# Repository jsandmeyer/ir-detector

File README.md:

## IR Reflection Detector

This provides resources to help you build an IR detector for use with O-scale model railroad track in order to detect passing trains for operating block signals.

It is designed to be placed beneath the tracks, to allow for the use of more realistic trackside accessories and buildings.

It emits and detects IR at 38KHz (though the frequency can be changed based on part choice).
This prevents background light from affecting function.

The original analog designs utilized a TLC555 CMOS timer.
The timer was unstable through stray capacitance caused by rail operation, and also likely by temperature fluctuations from the power supply.
Small microcontrollers like the ATTINY family are inexpensive, simple to program, and more stable even without an external clock.

The current versions utilize a switching power supply to avoid heat, so the device can be safely placed under track.
The input voltage is 18V RMS AC, which rectifies to 26V DC.
Since only 3-5 volts are needed for the circuit, power dissipation through a linear supply is excessive.

### Design Requirements

1. Must be able to handle 18V RMS AC (or a little more)
2. Must be able to handle rapid shutoff of power
3. Must avoid producing noticeable heat
4. Must fit hidden under track
   1. Shape limits (avoid track supports, power connectors, etc)
   2. Size limits (must not extend past track base, must have a way to feed wires)
   3. Some components must be aligned under a single oblong hole in track base
5. Emitter LED must be shrouded to avoid directly triggering detector
6. Must handle stray capacitance, excessive heat, and some signal interference
7. Must be small to reduce cost, especially when a 4-layer design is used

### Circuit Parts

1. MCU: Responsible for PWM to control the IR emitter, and controlling the relay when a reflection is detected.
2. Switching Power Supply: reduce up to 35VDC input to 3V output for the MCU, IR LED, and relay.
3. IR LED: an emitter running at ~70mA, and 50% duty cycle at 36-56KHz depending on detector part selection.
4. IR Detector: an IC containing both a detector and frequency detection logic, to ensure only correct-frequency light is detected.  36, 38, 40, or 56 KHz.
5. Relay: Controls AC (or DC) current from inputs to a normally-open and normally-closed output.
6. Trimmer: Controls duration of relay after IR is no longer detected.

### Design Versions

Some versions are skipped.
Those were only built on breadboard, or designed and considered non-viable.
Generally, each version is smaller or similar to the previous.

* Version 7: Used TLC556.  Had heat issues from power supply.
* Version 11: Used a switching power supply.  Still had stability issues.
* Version 13: Switched to use an ATTINY84.  Switched to 4-layer board.  Bridge rectifier could not handle rapid shutoff of some transformers.
* Version 14: Larger bridge rectifier.  Production model.  [Image](./resources/v14_production_model.jpg)
* Version 17: Updated layout, components (ATTINY20), and code.  Reduced to 2-layer board.  Manufacturing in process.

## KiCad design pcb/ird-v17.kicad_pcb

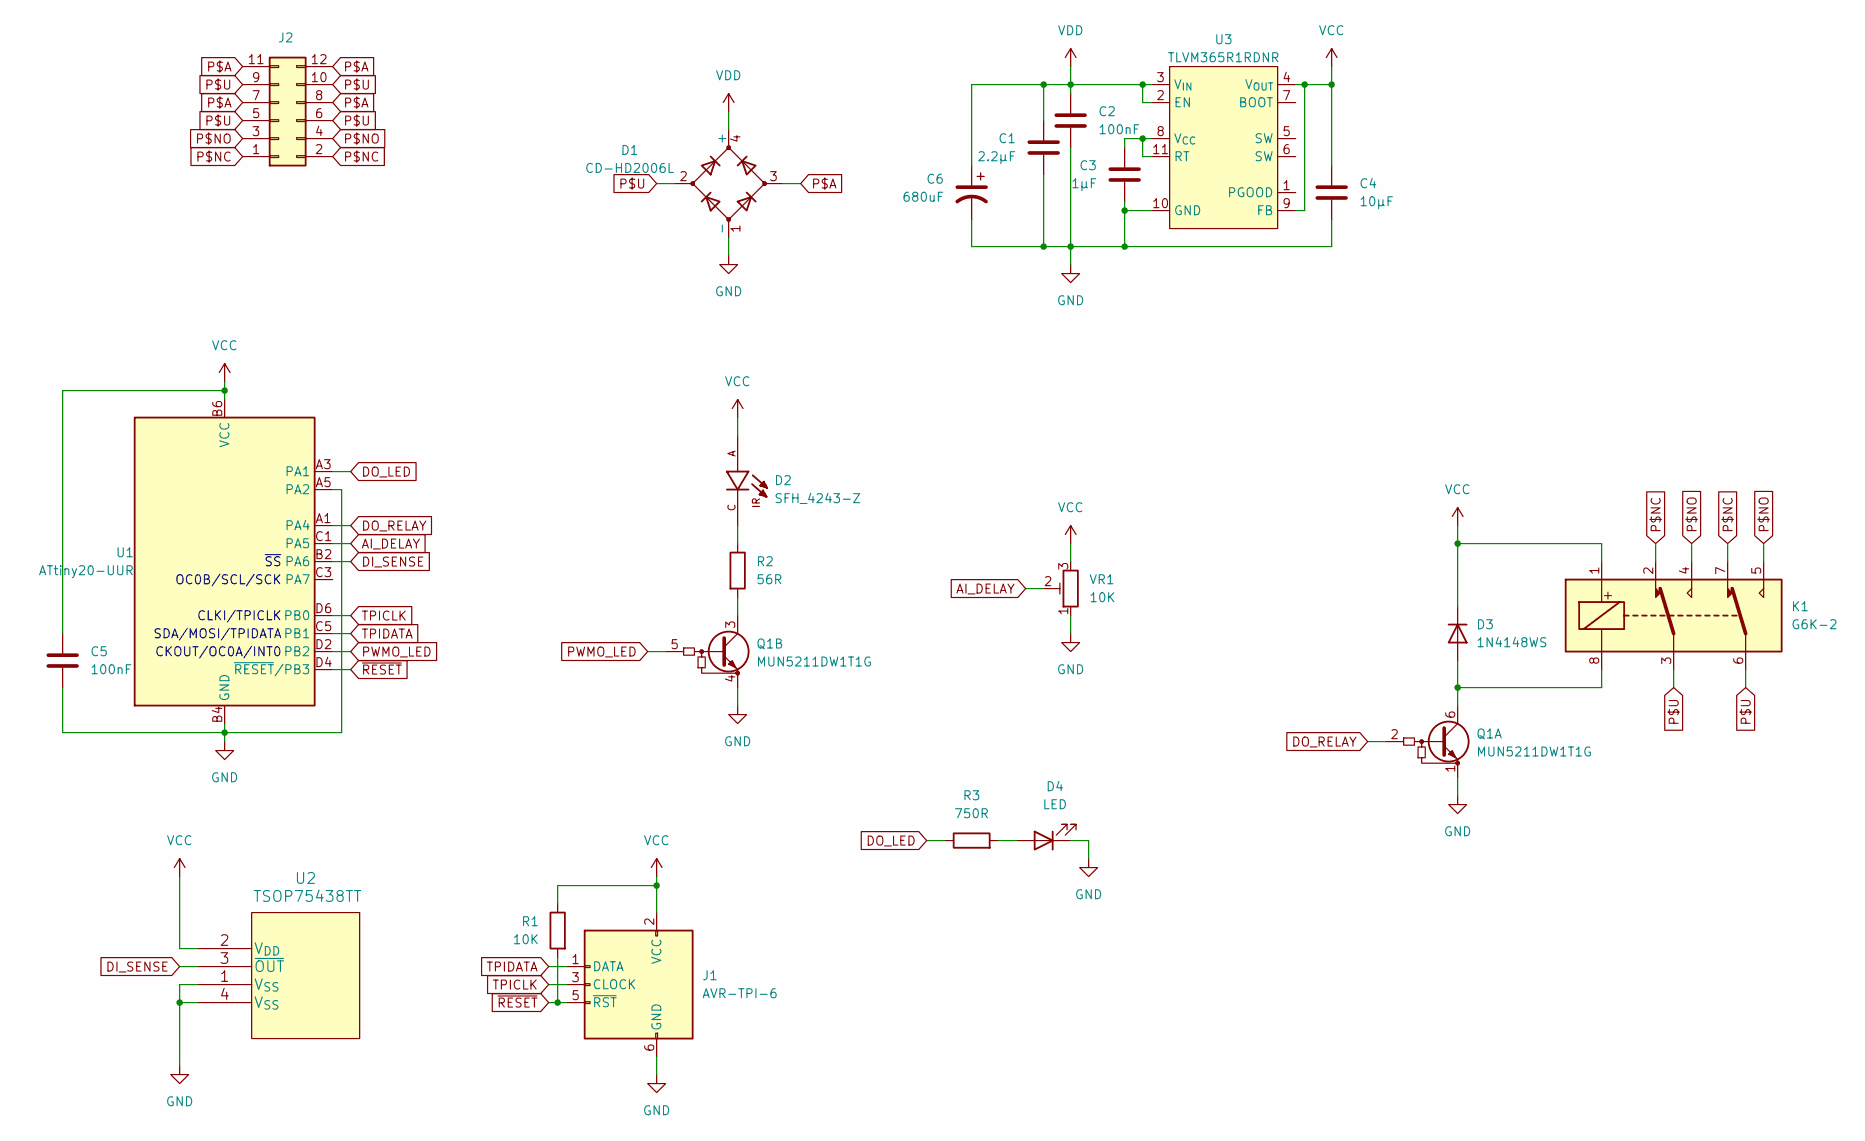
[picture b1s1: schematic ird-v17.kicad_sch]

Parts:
C1: 2.2µF; C_0805_2012Metric
C2, C5: 100nF; C_0402_1005Metric
C3: 1µF; C_0603_1608Metric
C4: 10µF; C_0805_2012Metric
C6: 680uF; CP_Radial_Long_Sideways_Flip
D1: CD-HD2006L; Diode_Bridge_Bourns_CD-HD2x
D2: SFH_4243-Z; LED_SFH_4243-Z; PARTREV 1.4
D3: 1N4148WS; D_SOD-323
D4: LED; LED_0603_1608Metric
J1: AVR-TPI-6; PinHeader_ISP_POGO
J2: Conn_02x06_Odd_Even; Kyocera_AVX_009296006202906
K1: G6K-2; Relay_DPDT_Omron_G6K-2G-Y
Q1: MUN5211DW1T1G; SOT-363_SC-70-6
R1: 10K; R_0402_1005Metric
R2: 56R; R_0402_1005Metric
R3: 750R; R_0402_1005Metric
U1: ATtiny20-UUR; WLCSP-12_1.403x1.555mm_Layout6x4_P0.4mm_Stagger
U2: TSOP75438TT; TSOP75438WTT
U3: TLVM365R1RDNR; QFN-FCMOD_TI_11C
VR1: 10K; Potentiometer_Bourns_TC42X_Vertical

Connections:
AI_DELAY: U1.C1 (PA5), VR1.2
DI_SENSE: U1.B2 (PA6), U2.3 (~OUT)
DO_LED: R3.1, U1.A3 (PA1)
DO_RELAY: Q1.2 (B1), U1.A1 (PA4)
GND: C1.2, C2.2, C3.2, C4.2, C5.2, C6.2, D1.1 (-), D4.1 (K), J1.6 (GND), Q1.1 (E1), Q1.4 (E2), U1.A5 (PA2), U1.B4 (GND), U2.1 (V_{SS}), U2.4 (V_{SS}), U3.10 (GND), VR1.1
unnamed: D2.C, R2.1
unnamed: D3.2 (A), K1.8, Q1.6 (C1)
unnamed: D4.2 (A), R3.2
unnamed: Q1.3 (C2), R2.2
unnamed: C3.1, U3.8 (V_{CC}), U3.11 (RT)
P$A: D1.3, J2.7, J2.8, J2.11, J2.12
P$NC: J2.1, J2.2, K1.2, K1.7
P$NO: J2.3, J2.4, K1.4, K1.5
P$U: D1.2, J2.5, J2.6, J2.9, J2.10, K1.3, K1.6
PWMO_LED: Q1.5 (B2), U1.D2 (PB2)
TPICLK: J1.3 (CLOCK), U1.D6 (PB0)
TPIDATA: J1.1 (DATA), U1.C5 (PB1)
VCC: C4.1, C5.1, D2.A, D3.1 (K), J1.2 (VCC), K1.1, R1.1, U1.B6 (VCC), U2.2 (V_{DD}), U3.4 (V_{OUT}), U3.9 (FB), VR1.3
VDD: C1.1, C2.1, C6.1, D1.4 (+), U3.2 (EN), U3.3 (V_{IN})
~RESET: J1.5 (~RST), R1.2, U1.D4 (~RESET/PB3)

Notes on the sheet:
CLKI/TPICLK
SDA/MOSI/TPIDATA
CKOUT/OC0A/INT0
~{SS}
OC0B/SCL/SCK

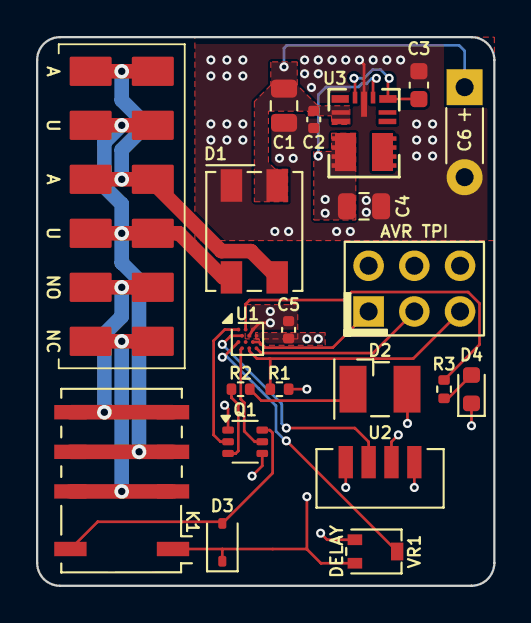
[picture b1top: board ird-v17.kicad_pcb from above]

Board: 2 copper layers, 25.4 x 30.5 mm, 21 parts (0 on the bottom side), 20 nets.

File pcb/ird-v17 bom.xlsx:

Ref | Value | SKU | Status | $/1 | $/3 | $/10
C1 | 2.2µF | GCM31CR71H225KA55L |  | 0.33 | 0.99 | 1.98
C2 | 100nF | GCM155R71H104KE02D |  | 0.1 | 0.30000000000000004 | 0.31
C3 | 1µF | CGA3E1X7R1V105K080AC |  | 0.23 | 0.69000000000000006 | 1.31
C4 | 10µF | GRM21BR61E106MA73L |  | 0.17 | 0.51 | 0.99
C5 | 100nF | GCM155R71H104KE02D |  | 0.1 | 0.30000000000000004 | 0.31
C6 | 680µF | 860020575016 |  | 0.61 | 1.83 | 6.01
D1 | -AA+ | CD-HD2006L |  | 0.98 | 2.94 | 7.33
D2 | IR | SFH_4243-Z |  | 0.65 | 1.9500000000000002 | 4.5199999999999996
D3 | Diode | 1N4148WS |  | 0.13 | 0.39 | 0.92
D4 | LED | SML-LXFP0603UWW-TR | OPTIONAL | 0.44 | 1.32 | 2.99
J1 | TPI POGO | Atmel 6-pin TPI connector | DNP | 0 | 0 | 0
J2 | Conn 2x6 | 9296006202906 |  | 0.81 | 2.4300000000000002 | 6.86
K1 | Relay DPDT | G6K-2G-Y-TR DC5 |  | 4.21 | 12.629999999999999 | 39.79
Q1 | NPN 10K 10K x2 | MUN5211DW1T1G |  | 0.23 | 0.69000000000000006 | 1.39
R1 | 10K | RCS040210K0FKED |  | 0.11 | 0.33 | 0.52
R2 | 56R | RCS040256R0FKED |  | 0.12 | 0.36 | 0.57999999999999996
R3 | 750R | RCS0402750RFKED | OPTIONAL | 0.12 | 0.36 | 0.57999999999999996
U1 | ATTiny20 | ATTINY20-UUR |  | 1.18 | 3.54 | 11.8
U2 | IR Detector | TSOP75438TT |  | 1.34 | 4.0200000000000005 | 11.22
U3 | 5V SMPS | TLVM365R1RDNR |  | 2.2799999999999998 | 6.84 | 16.87
VR1 | 10K | TC42X-2-103E |  | 0.45 | 1.35 | 3.79
PCB | PCB | PCB | PCB | 2 | 6 | 20
Total |  |  |  | 16.589999999999996 | 49.77 | 140.07

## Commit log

2025-03-15 Rearrange pins
2025-03-16 PCB project update
2025-03-16 Clean up debug
2025-03-16 Add comments
2025-03-20 PCB update
2025-03-20 Readme update
2025-03-20 Update BOM
2025-05-04 Update to use 5V for consistent ATTINY20 programming
